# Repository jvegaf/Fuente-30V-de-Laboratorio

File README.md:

# Fuente-30V-de-Laboratorio
Esquema en kicad de la fuente de alimentacion para laboratorio creada por @Terrazocultor en su blog

http://100ciaencasa.blogspot.com.es/2014/06/circuitos-utiles-05-fuente-de.html

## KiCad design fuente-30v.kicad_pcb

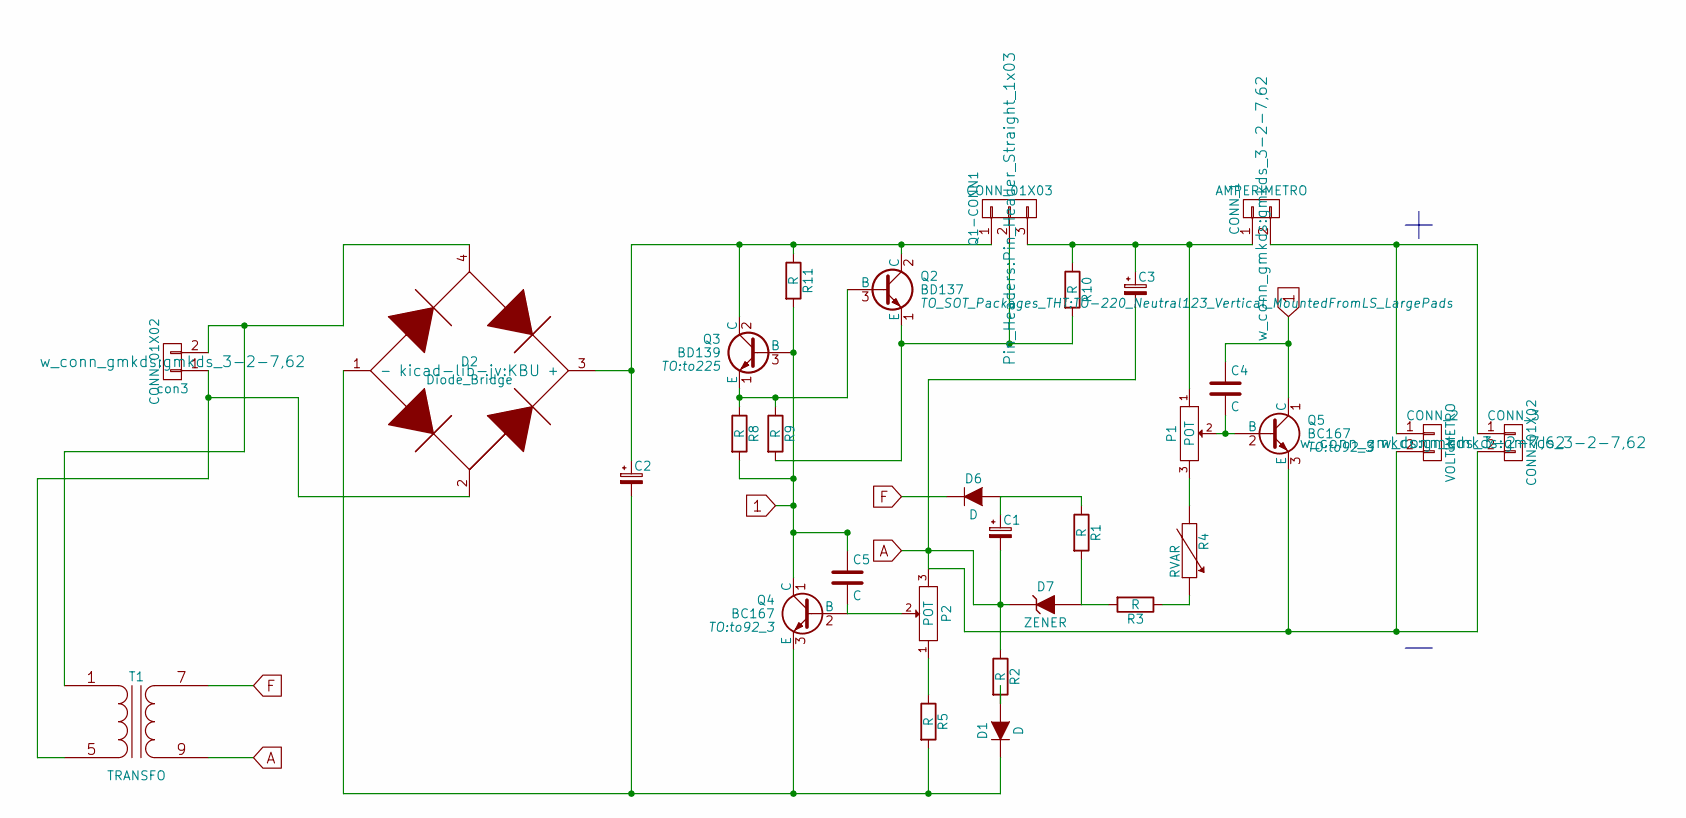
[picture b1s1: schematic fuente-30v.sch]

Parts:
C1: Elko_vert_11.5x8mm_RM3.5
C2: CP_22x25mm
C3: Elko_vert_11x5mm_RM2
C4, C5: C; C_Disc_D3_P2.5
CONN_1: AMPERIMETRO; gmkds_3-2-7,62
CONN_2: VOLTIMETRO; gmkds_3-2-7,62
CONN_3: CONN_01X02; gmkds_3-2-7,62
D1: D; Diode_DO-201AD_Horizontal_RM15
D2: Diode_Bridge; KBU
D6: D; Diode_DO-41_SOD81_Horizontal_RM10
D7: ZENER; Diode_DO-41_SOD81_Vertical_KathodeUp
P1, P2: POT; Pin_Header_Straight_1x03
Q1-CONN1: CONN_01X03; Pin_Header_Straight_1x03
Q2: BD137; TO-220_Neutral123_Vertical_MountedFromLS_LargePads
Q3: BD139; to225
Q4, Q5: BC167; to92_3
R1, R3, R5, R8, R9, R10, R11: R; Resistor_Horizontal_RM10mm
R2: R; Resistor_Ceramic_Horizontal_L36mm-W11mm-H10mm-p45mm
R4: RVAR; trimmer_piher_pt6xv
T1: TRANSFO; Transfotype4
con3: CONN_01X02; gmkds_3-2-7,62

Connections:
1: C4.1, C5.1, Q3.3 (B), Q4.1 (C), Q5.1 (C), R8.2, R11.2
A: C1.2, C3.2, CONN_2.2, CONN_3.2, D7.1 (K), P2.3, Q5.3 (E), R2.1, T1.9 (SA)
F: D6.1 (K), T1.7 (SB)
unnamed: C1.1, D6.2 (A), R1.1
unnamed: C2.1, D2.3 (+), Q1-CONN1.1, Q2.2 (C), Q3.2 (C), R11.1
unnamed: C2.2, D1.1 (K), D2.1 (-), Q4.3 (E), R5.2
unnamed: C3.1, CONN_1.1, P1.1, Q1-CONN1.3, R10.1
unnamed: C4.2, P1.2, Q5.2 (B)
unnamed: C5.2, P2.2, Q4.2 (B)
unnamed: CONN_1.2, CONN_2.1, CONN_3.1
unnamed: D1.2 (A), R2.2
unnamed 11: D2.2, T1.5 (AB), con3.1; also elsewhere on the board
unnamed 12: D2.4, T1.1 (AA), con3.2; also elsewhere on the board
unnamed: D7.2 (A), R1.2, R3.2
unnamed: P1.3, R4.2
unnamed: P2.1, R5.1
unnamed: Q1-CONN1.2, Q2.1 (E), R9.2, R10.2
unnamed: Q2.3 (B), Q3.1 (E), R8.1, R9.1
unnamed: R3.1, R4.1

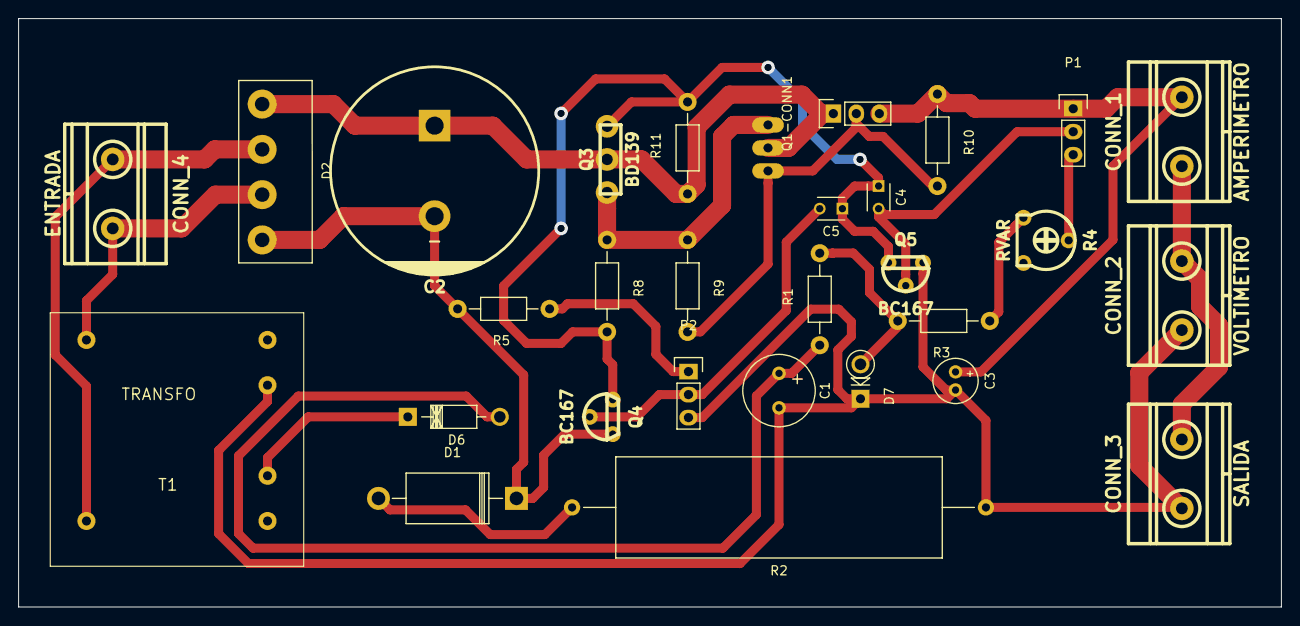
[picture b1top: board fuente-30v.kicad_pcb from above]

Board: 2 copper layers, 139.5 x 65.0 mm, 30 parts (1 on the bottom side), 19 nets.

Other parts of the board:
CONN_4: ENTRADA; gmkds_3-2-7,62

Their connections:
unnamed 11: CONN_4.1; also elsewhere on the board
unnamed 12: CONN_4.2; also elsewhere on the board

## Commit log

2015-11-04 version 1.0
2015-11-08 version 1.1: arreglados los problemas de conexion
2015-11-30 change track width to 1 mm
2015-11-30 update readme with images
2015-12-02 checked and fixed design rules
2015-12-11 cambio de ancho de algunas pistas
